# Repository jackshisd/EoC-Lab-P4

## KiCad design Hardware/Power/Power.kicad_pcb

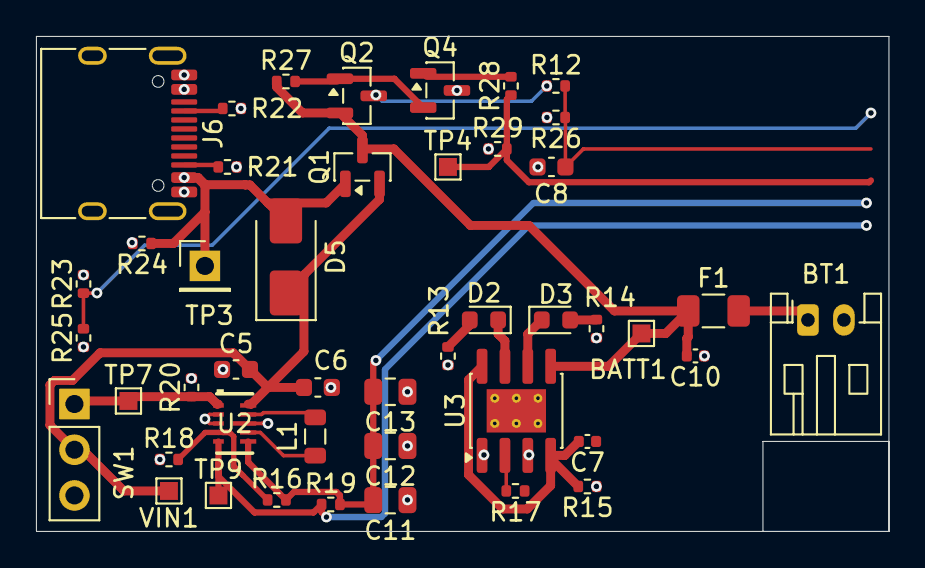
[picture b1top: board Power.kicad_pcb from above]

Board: 4 copper layers, 47.4 x 27.5 mm, 45 parts (0 on the bottom side), 25 nets.

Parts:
BATT1: TestPoint; TestPoint_Pad_1.0x1.0mm
BT1: Battery_Cell; JST_PH_S2B-PH-K_1x02_P2.00mm_Horizontal
C5, C6: 10uF; C_0603_1608Metric
C7, C10: 10uF; C_0402_1005Metric
C8: 100nF; C_0603_1608Metric
C11, C12, C13: 22uF; C_0805_2012Metric
D2, D3: LED; LED_0603_1608Metric
D5: SS14; D_SMA
F1: Fuse; Fuse_1206_3216Metric
J6: USB_C_Receptacle_USB2.0_16P; USB_C_Receptacle_HRO_TYPE-C-31-M-12
L1: 0.47uH DFE201612E; L_0805_2012Metric
Q1, Q2, Q4: AO3401A; SOT-23
R12, R18, R23, R24, R26, R27, R29: 100k; R_0402_1005Metric
R13, R14: 10k; R_0402_1005Metric
R15: 0; R_0402_1005Metric
R16: 560k; R_0402_1005Metric
R17: 4.7k; R_0402_1005Metric
R19, R20: 1M; R_0402_1005Metric
R21, R22: 5.1k; R_0402_1005Metric
R25: 150k; R_0402_1005Metric
R28: 1k; R_0402_1005Metric
SW1: SW_SPST; PinHeader_1x03_P2.54mm_Vertical
TP3: TestPoint; PinHeader_1x01_P2.54mm_Vertical
TP4, TP7, TP9: TestPoint; TestPoint_Pad_1.0x1.0mm
U2: TPS63802
U3: TP4056-42-ESOP8; SOIC-8-1EP_3.9x4.9mm_P1.27mm_EP2.41x3.3mm_ThermalVias
VIN1: TestPoint; TestPoint_Pad_1.0x1.0mm

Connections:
+3.3V: C11.2, C12.2, C13.2, R16.2, R19.2, U2.6 (VOUT)
+5V_USB: D5.2 (A), J6.A4 (VBUS), J6.A9 (VBUS), J6.B4 (VBUS), J6.B9 (VBUS), Q1.1 (G), R13.2, R14.2, R15.1, R23.2, R24.1, TP3.1 (1_1)
+BATT: BATT1.1 (1_1), C10.2, F1.1, Q1.3 (D), Q2.2 (S), R27.1, U3.5 (BAT)
/PG_3V3: R19.1, TP9.1 (1_1), U2.5 (PG)
/USB_DET: R23.1, R25.2
/VBAT_SENSE: C8.2, R12.2, R26.1
/VBAT_SENSE_EN: R28.1, R29.2, TP4.1 (1_1)
GND: BT1.2 (-), C5.1, C6.1, C7.1, C8.1, C10.1, C11.1, C12.1, C13.1, J6.A1 (GND), J6.A12 (GND), J6.B1 (GND), J6.B12 (GND), Q4.3 (D), R17.1, R18.1, R20.2, R21.2, R22.2, R24.2, R25.1, R26.2, R29.1, U2.2 (MODE), U2.3 (AGND), U2.8 (GND), U3.1 (TEMP), U3.3 (GND), U3.9 (EPAD)
unnamed: BT1.1 (+), F1.2
unnamed: D2.2 (A), R13.1
unnamed: D2.1 (K), U3.7 (~CHRG)
unnamed: D3.2 (A), R14.1
unnamed: D3.1 (K), U3.6 (~STDBY)
unnamed: J6.A5 (CC1), R22.1
unnamed: J6.B5 (CC2), R21.1
unnamed: Q2.3 (D), R12.1
unnamed: Q2.1 (G), Q4.2 (S), R27.2
unnamed: Q4.1 (G), R28.2
unnamed: R20.1, SW1.1 (A), TP7.1 (1_1), U2.1 (EN)
unnamed: R16.1, R18.2, U2.4 (FB)
unnamed: L1.2, U2.9 (L1)
unnamed: L1.1, U2.7 (L2)
unnamed: C7.2, R15.2, U3.4 (V_{CC}), U3.8 (CE)
unnamed: R17.2, U3.2 (PROG)
VIN: C5.2, C6.2, D5.1 (K), Q1.2 (S), SW1.2 (B), U2.10 (VIN), VIN1.1 (1_1)

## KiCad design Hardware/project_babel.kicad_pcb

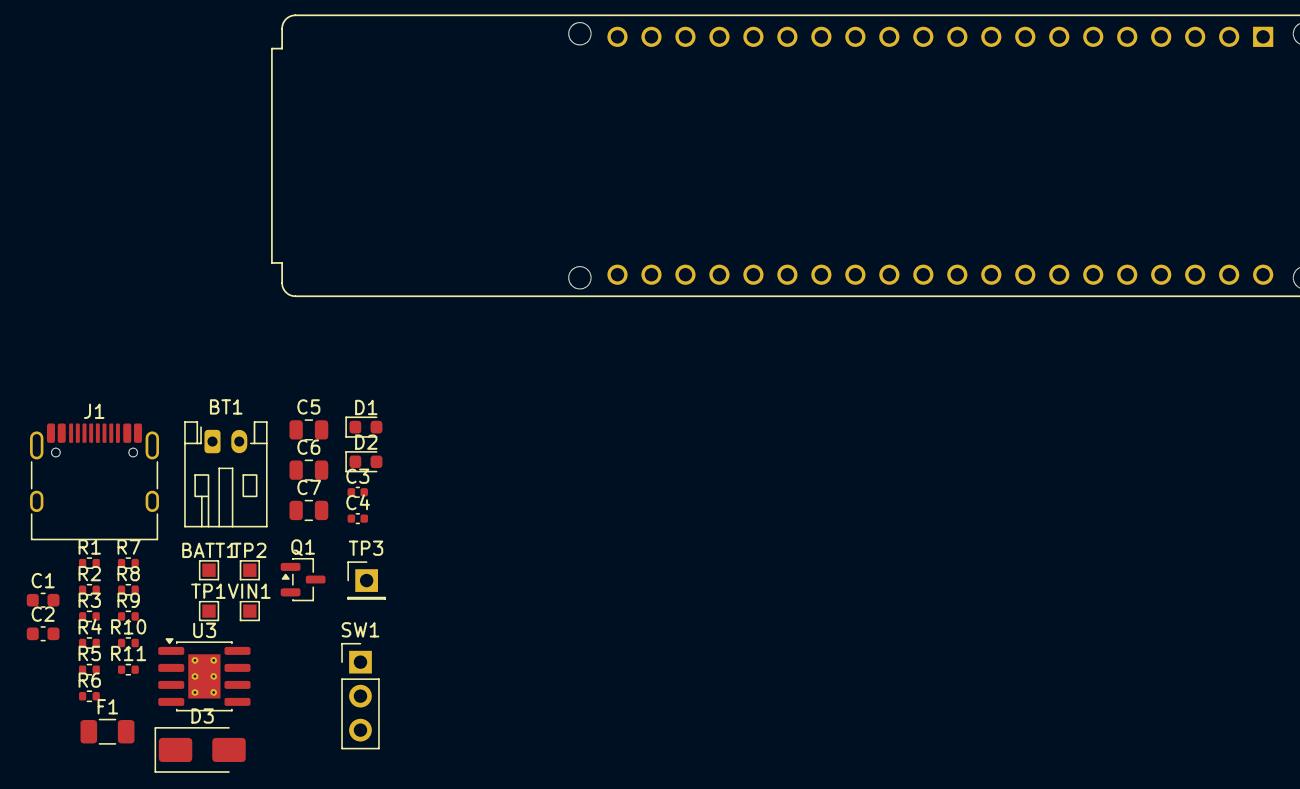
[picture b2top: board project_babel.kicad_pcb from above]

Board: 2 copper layers, 33 parts (0 on the bottom side), 17 nets, no tracks yet.

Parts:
BATT1: TestPoint; TestPoint_Pad_1.0x1.0mm
BT1: Battery_Cell; JST_PH_S2B-PH-K_1x02_P2.00mm_Horizontal
C1, C2: 10uF; C_0603_1608Metric
C3, C4: 10uF; C_0402_1005Metric
C5, C6, C7: 22uF; C_0805_2012Metric
D1, D2: LED; LED_0603_1608Metric
D3: SS14; D_SMA
F1: Fuse; Fuse_1206_3216Metric
J1: USB_C_Receptacle_USB2.0_16P; USB_C_Receptacle_HRO_TYPE-C-31-M-12
Q1: AO3401A; SOT-23
R1, R2: 10k; R_0402_1005Metric
R3, R8: 1M; R_0402_1005Metric
R4: 0; R_0402_1005Metric
R5: 560k; R_0402_1005Metric
R6: 4.7k; R_0402_1005Metric
R7, R11: 100k; R_0402_1005Metric
R9, R10: 5.1k; R_0402_1005Metric
SW1: SW_SPST; PinHeader_1x03_P2.54mm_Vertical
TP1, TP2: TestPoint; TestPoint_Pad_1.0x1.0mm
TP3: TestPoint; PinHeader_1x01_P2.54mm_Vertical
U1: ESP32-P4-ETH; MODULE_ESP32-P4-ETH
U3: TP4056-42-ESOP8; SOIC-8-1EP_3.9x4.9mm_P1.27mm_EP2.41x3.3mm_ThermalVias
VIN1: TestPoint; TestPoint_Pad_1.0x1.0mm

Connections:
+3.3V: C5.2, C6.2, C7.2, R5.2, R8.2
+5V_USB: D3.2 (A), J1.A4 (VBUS), J1.A9 (VBUS), J1.B4 (VBUS), J1.B9 (VBUS), Q1.1 (G), R1.2, R2.2, R4.1, R11.1, TP3.1 (1_1)
+BATT: BATT1.1 (1_1), C4.2, F1.1, Q1.3 (D), U3.5 (BAT)
GND: BT1.2 (-), C1.1, C2.1, C3.1, C4.1, C5.1, C6.1, C7.1, J1.A1 (GND), J1.A12 (GND), J1.B1 (GND), J1.B12 (GND), R3.2, R6.1, R7.1, R9.2, R10.2, R11.2, U1.3 (GND), U1.8 (GND), U1.13 (GND), U1.18 (GND), U1.23 (GND), U1.28 (GND), U1.33 (GND), U1.38 (GND), U3.1 (TEMP), U3.3 (GND), U3.9 (EPAD)
unnamed: BT1.1 (+), F1.2
unnamed: D1.2 (A), R1.1
unnamed: D1.1 (K), U3.7 (~CHRG)
unnamed: D2.2 (A), R2.1
unnamed: D2.1 (K), U3.6 (~STDBY)
unnamed: J1.A5 (CC1), R10.1
unnamed: J1.B5 (CC2), R9.1
unnamed: R3.1, SW1.1 (A), TP1.1 (1_1)
unnamed: R5.1, R7.2
unnamed: R8.1, TP2.1 (1_1)
unnamed: C3.2, R4.2, U3.4 (V_{CC}), U3.8 (CE)
unnamed: R6.2, U3.2 (PROG)
VIN: C1.2, C2.2, D3.1 (K), Q1.2 (S), SW1.2 (B), VIN1.1 (1_1)
